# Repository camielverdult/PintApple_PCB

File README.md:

# PintApple PCB

This is version 2 of the PCB made for Project Integration in Applied Computer Science year 2 at Saxion Enschede.

## Features

| Function | Main part                                                | Comments |
|----------|-----------------------------------------------------|----------|
| MCU | [ESP32-S2-WROVER](https://www.espressif.com/sites/default/files/documentation/esp32-s2-wroom_esp32-s2-wroom-i_datasheet_en.pdf) | |
| Power | [XC6222B331MR-G](https://www.farnell.com/datasheets/3118383.pdf) | 3.3V, 700mA |
| Accelerometer | [MMA8652FCR1](https://www.farnell.com/datasheets/1869253.pdf) | |
| Display | [SSD1306 OLED](https://cdn-shop.adafruit.com/datasheets/SSD1306.pdf) | |
| Microphone | [MAX9814](https://www.adafruit.com/product/1713) | |
| SD card | [472192001](https://www.molex.com/molex/products/part-detail/memory_card_socket/0472192001) | |
| Heartbeat | [MAX30102](http://www.arduinoproducts.net/products/mh-et-live-max30102-heart-rate-sensor-module-puls-detection-blood-oxygen-concentration-test-for-arduino-ultra-low-power/) | |

## Renders

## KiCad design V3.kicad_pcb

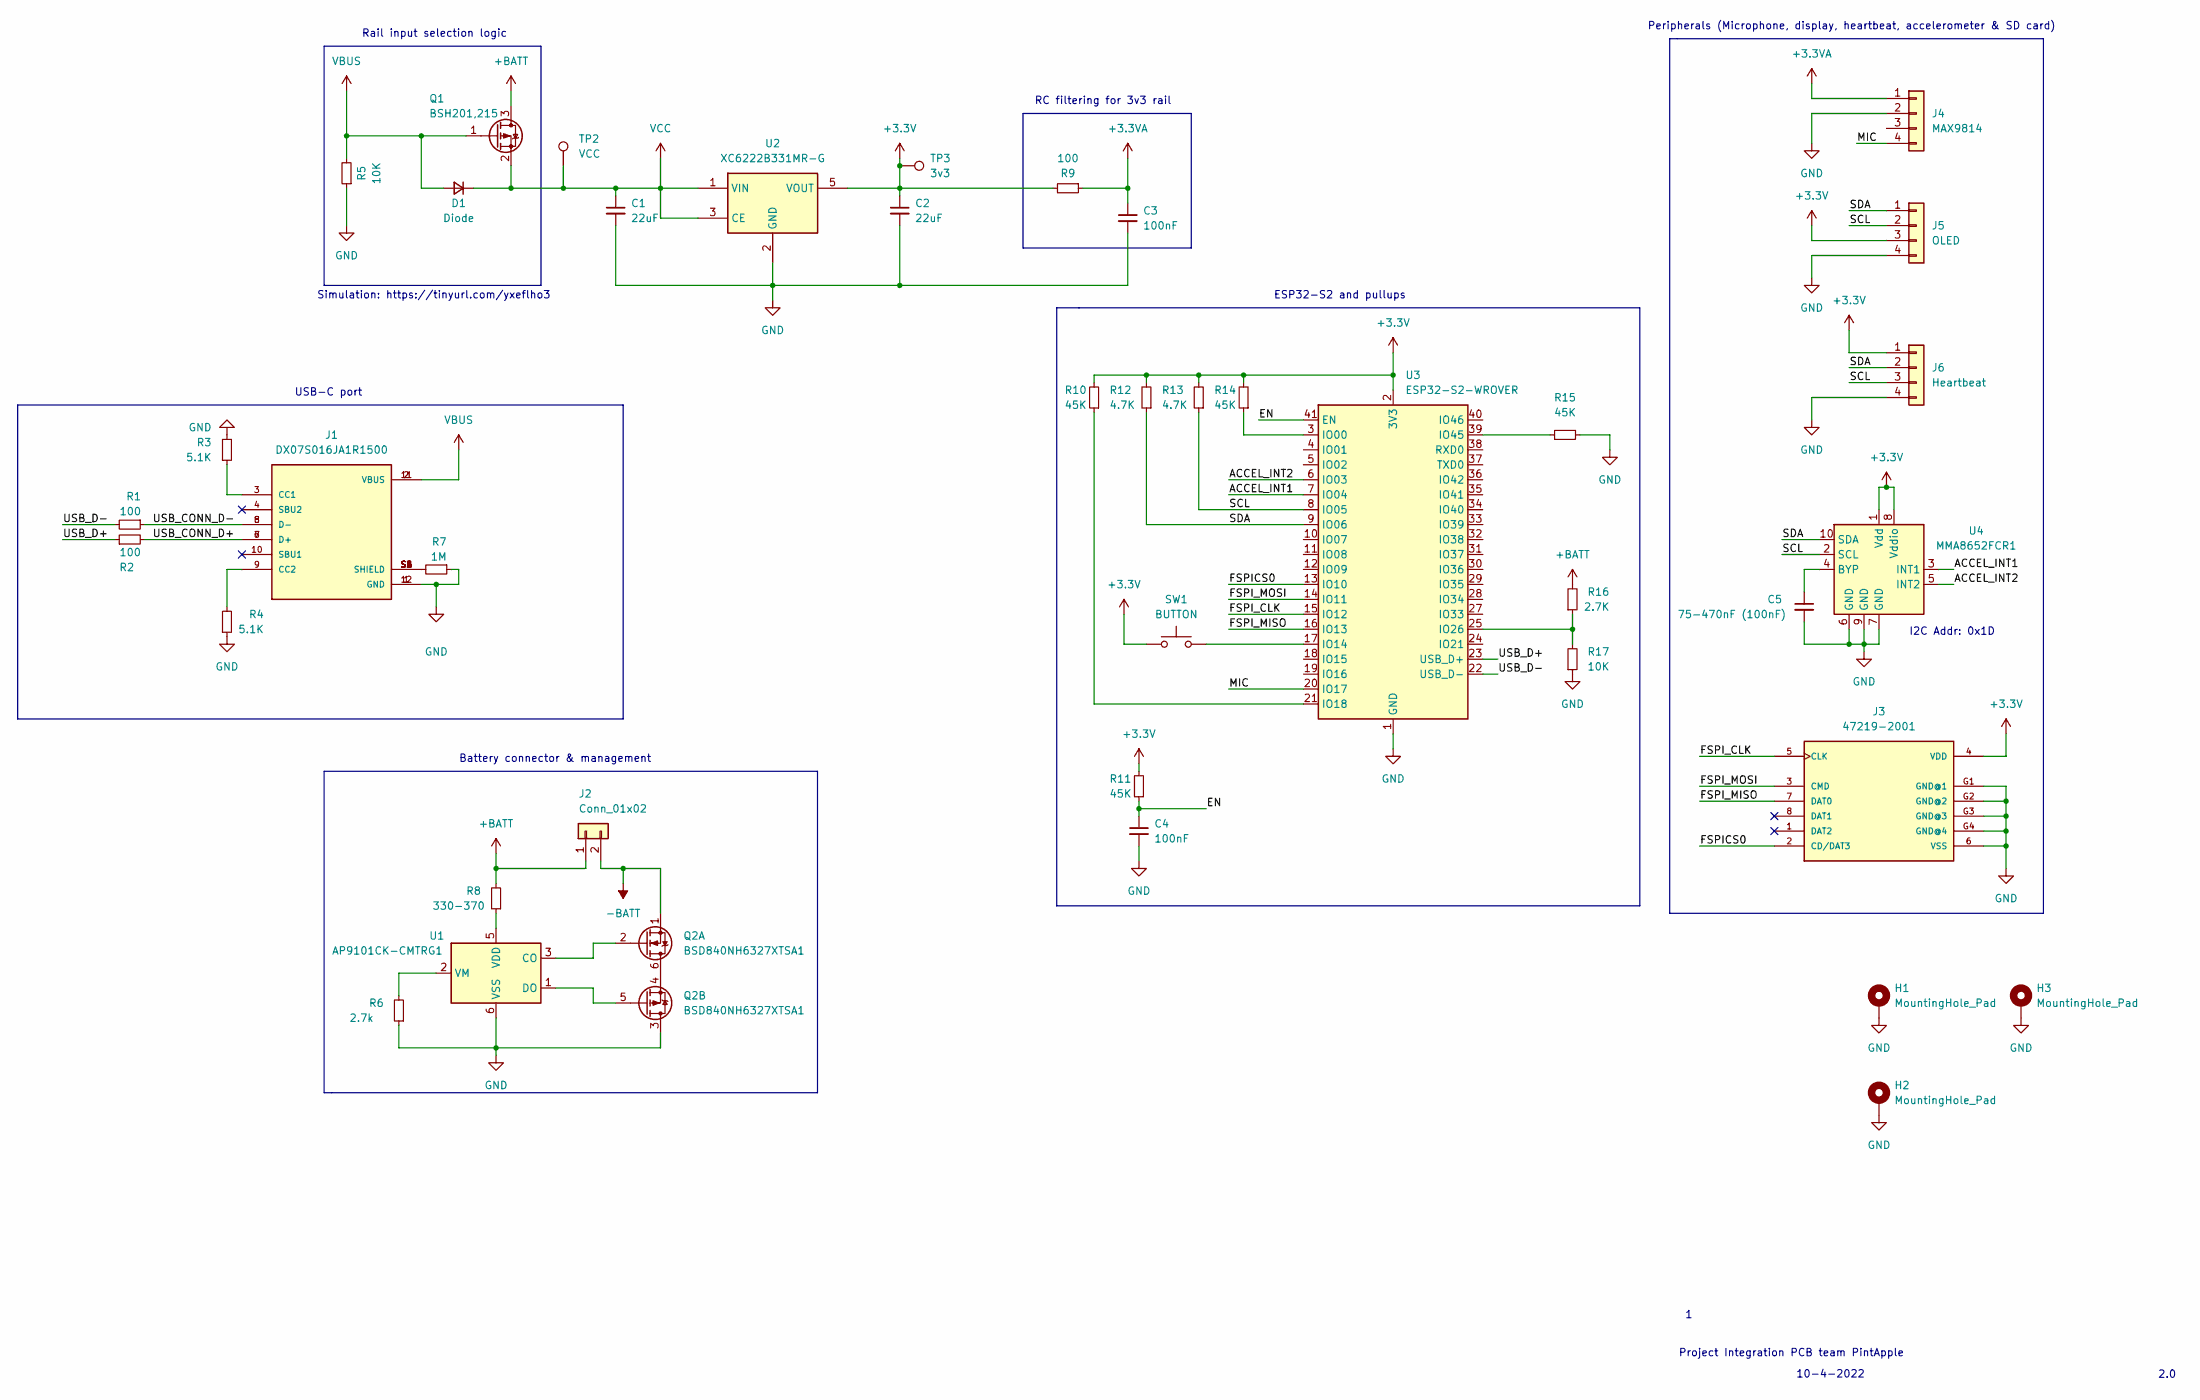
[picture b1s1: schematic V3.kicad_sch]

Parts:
C1, C2: 22uF; C_1206_3216Metric
C3, C4: 100nF; C_1206_3216Metric
C5: 75-470nF (100nF); C_1206_3216Metric
D1: Diode; D_SOD-123
H1, H2, H3: MountingHole_Pad; MountingHole_2.2mm_M2_Pad
J1: DX07S016JA1R1500; JAE_DX07S016JA1R1500; PARTREV 1
J2: Conn_01x02; PinHeader_1x02_P2.54mm_Vertical
J3: 47219-2001; MOLEX_47219-2001
J4: MAX9814; PinHeader_1x04_P2.54mm_Vertical
J5: OLED; PinHeader_1x04_P2.54mm_Vertical
J6: Heartbeat; PinHeader_1x04_P2.54mm_Vertical
Q1: BSH201,215; SOT-23
Q2: BSD840NH6327XTSA1; SOT-363_SC-70-6
R1, R2, R9: 100; R_1206_3216Metric
R3, R4: 5.1K; R_1206_3216Metric
R5, R17: 10K; R_1206_3216Metric
R6: 2.7k; R_1206_3216Metric
R7: 1M; R_1206_3216Metric
R8: 330-370; R_1206_3216Metric
R10, R11, R14, R15: 45K; R_1206_3216Metric
R12, R13: 4.7K; R_1206_3216Metric
R16: 2.7K; R_1206_3216Metric
SW1: BUTTON; SW_Push_1P1T_NO_CK_KSC6xxJ
TP2: VCC; TestPoint_Pad_D1.0mm
TP3: 3v3; TestPoint_Pad_D1.0mm
U1: AP9101CK-CMTRG1; SOT-23-6
U2: XC6222B331MR-G; SOT-23-5
U3: ESP32-S2-WROVER
U4: MMA8652FCR1; DFN-10_2x2mm_P0.4mm

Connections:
+3.3VA: C3.1, J4.1, R9.1
+3V3: C2.1, J3.4 (VDD), J5.3, J6.1, R9.2, R10.2, R11.2, R12.2, R13.2, R14.2, SW1.1, TP3.1, U2.5 (VOUT), U3.2 (3V3), U4.1 (Vdd), U4.8 (Vddio)
+BATT: J2.1, Q1.3 (D), R8.2, R16.2
-BATT: J2.2, Q2.1 (SN)
/ACCEL_INT1: U3.7 (IO04), U4.3 (INT1)
/ACCEL_INT2: U3.6 (IO03), U4.5 (INT2)
/EN: C4.1, R11.1, U3.41 (EN)
/FSPICS0: J3.2 (CD/DAT3), U3.13 (IO10)
/FSPI_CLK: J3.5 (CLK), U3.15 (IO12)
/FSPI_MISO: J3.7 (DAT0), U3.16 (IO13)
/FSPI_MOSI: J3.3 (CMD), U3.14 (IO11)
/MIC: J4.4, U3.20 (IO17)
/SCL: J5.2, J6.3, R13.1, U3.8 (IO05), U4.2 (SCL)
/SDA: J5.1, J6.2, R12.1, U3.9 (IO06), U4.10 (SDA)
/USB_CONN_D+: J1.6 (D+), J1.7 (D+), R2.2
/USB_CONN_D-: J1.5 (D-), J1.8 (D-), R1.1
/USB_D+: R2.1, U3.23 (USB_D+)
/USB_D-: R1.2, U3.22 (USB_D-)
GND: C1.2, C2.2, C3.2, C4.2, C5.2, H1.1, H2.1, H3.1, J1.1 (GND), J1.12 (GND), J3.6 (VSS), J3.G1 (GND@1), J3.G2 (GND@2), J3.G3 (GND@3), J3.G4 (GND@4), J4.2, J5.4, J6.4, Q2.3 (DP), R3.2, R4.1, R5.1, R6.1, R7.1, R15.2, R17.1, U1.6 (VSS), U2.2 (GND), U3.1 (GND), U3.26 (GND), U3.42 (GND), U3.43 (GND), U4.6 (GND), U4.7 (GND), U4.9 (GND)
unnamed: C5.1, U4.4 (BYP)
unnamed: J1.3 (CC1), R3.1
unnamed: J1.9 (CC2), R4.2
unnamed: J1.S1 (SHIELD), J1.S2 (SHIELD), J1.S3 (SHIELD), J1.S4 (SHIELD), J1.S5 (SHIELD), J1.S6 (SHIELD), R7.2
unnamed: Q2.2 (GN), U1.3 (CO)
unnamed: Q2.4 (SP), Q2.6 (DN)
unnamed: Q2.5 (GP), U1.1 (DO)
unnamed: R6.2, U1.2 (VM)
unnamed: R8.1, U1.5 (VDD)
unnamed: R10.1, U3.21 (IO18)
unnamed: R14.1, U3.3 (IO00)
unnamed: R15.1, U3.39 (IO45)
unnamed: R16.1, R17.2, U3.25 (IO26)
unnamed: SW1.2, U3.17 (IO14)
VBUS: D1.2 (A), J1.2 (VBUS), J1.11 (VBUS), Q1.1 (G), R5.2
VCC: C1.1, D1.1 (K), Q1.2 (S), TP2.1, U2.1 (VIN), U2.3 (CE)

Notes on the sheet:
I2C Addr: 0x1D
Battery connector & management
10-4-2022
Simulation: https://tinyurl.com/yxeflho3
USB-C port
ESP32-S2 and pullups
Project Integration PCB team PintApple
Peripherals (Microphone, display, heartbeat, accelerometer & SD card)
Rail input selection logic
RC filtering for 3v3 rail
2.0

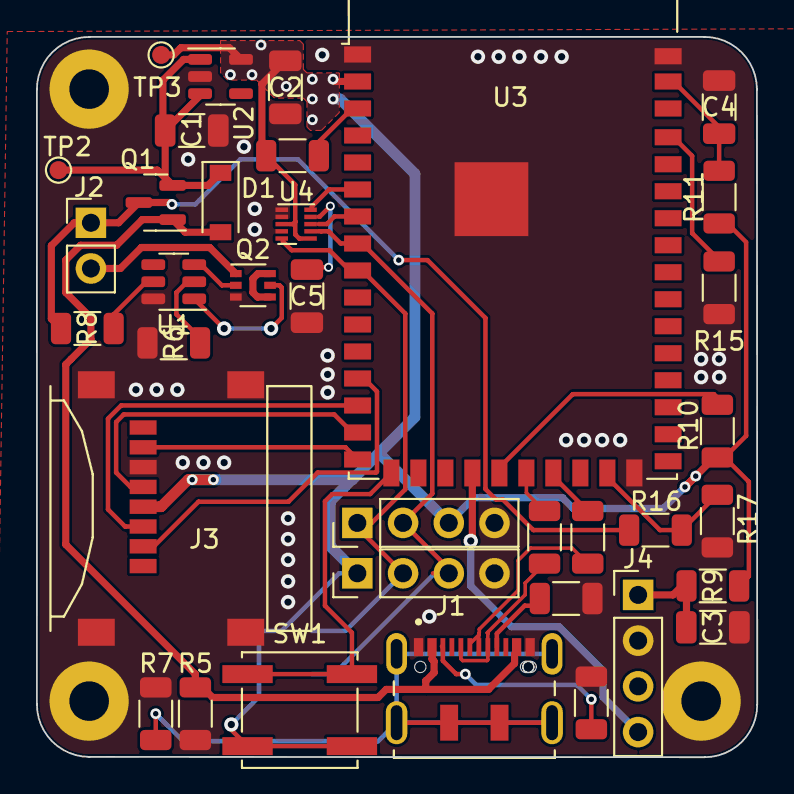
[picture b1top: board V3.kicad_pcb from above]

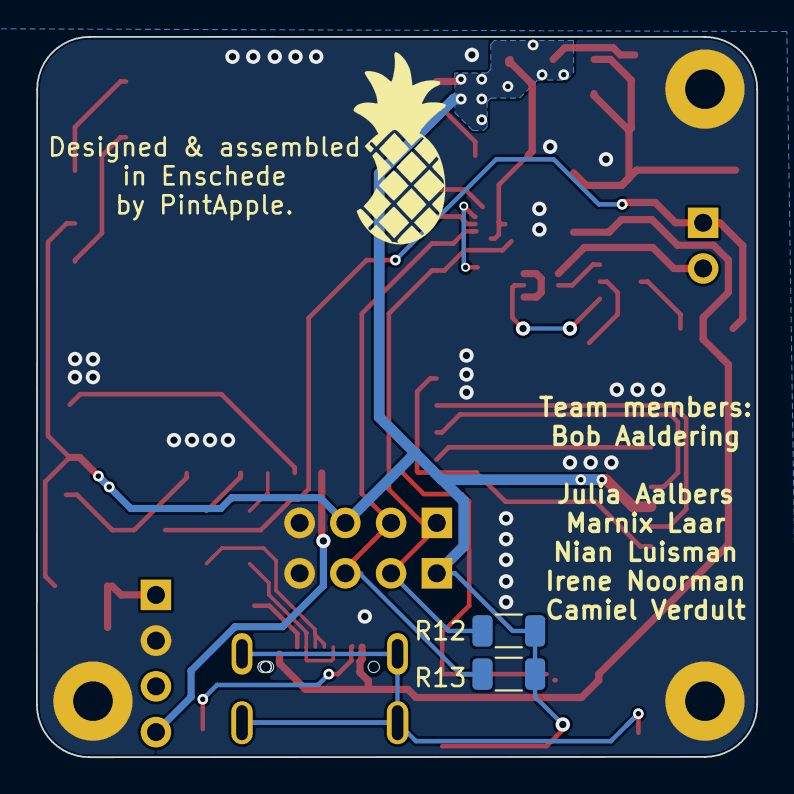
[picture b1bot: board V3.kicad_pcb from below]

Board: 2 copper layers, 40.0 x 40.0 mm, 41 parts (2 on the bottom side), 35 nets.

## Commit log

2022-04-09 Finalise schematic and start routing
2022-04-09 Route power
2022-04-10 Finish routing and export gerbers
2022-04-10 Add 3d models, pcb & schematic touch up, graphics, update gerbers and add step file
2022-04-10 Organisation
2022-04-10 Switch out micro USB for USB-C
2022-04-11 Add USB-C port
2022-04-11 Update 3d model
2022-04-11 Update gerbers
2022-04-11 Add missing vias and update gerbers
2022-04-25 v3.1
2022-05-09 Update pdfs
